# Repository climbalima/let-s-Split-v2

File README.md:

[Easier to use dimensions document](https://cad.onshape.com/documents/c6e5ae250d1e24fe46c9ef6c/w/d69f7049c0921df3d2b241f9/e/8fe93acf5ce0a952a4563ee0) 

Just click on any two lines/points, and read the dimensions bottom left. Space to unselect everything.

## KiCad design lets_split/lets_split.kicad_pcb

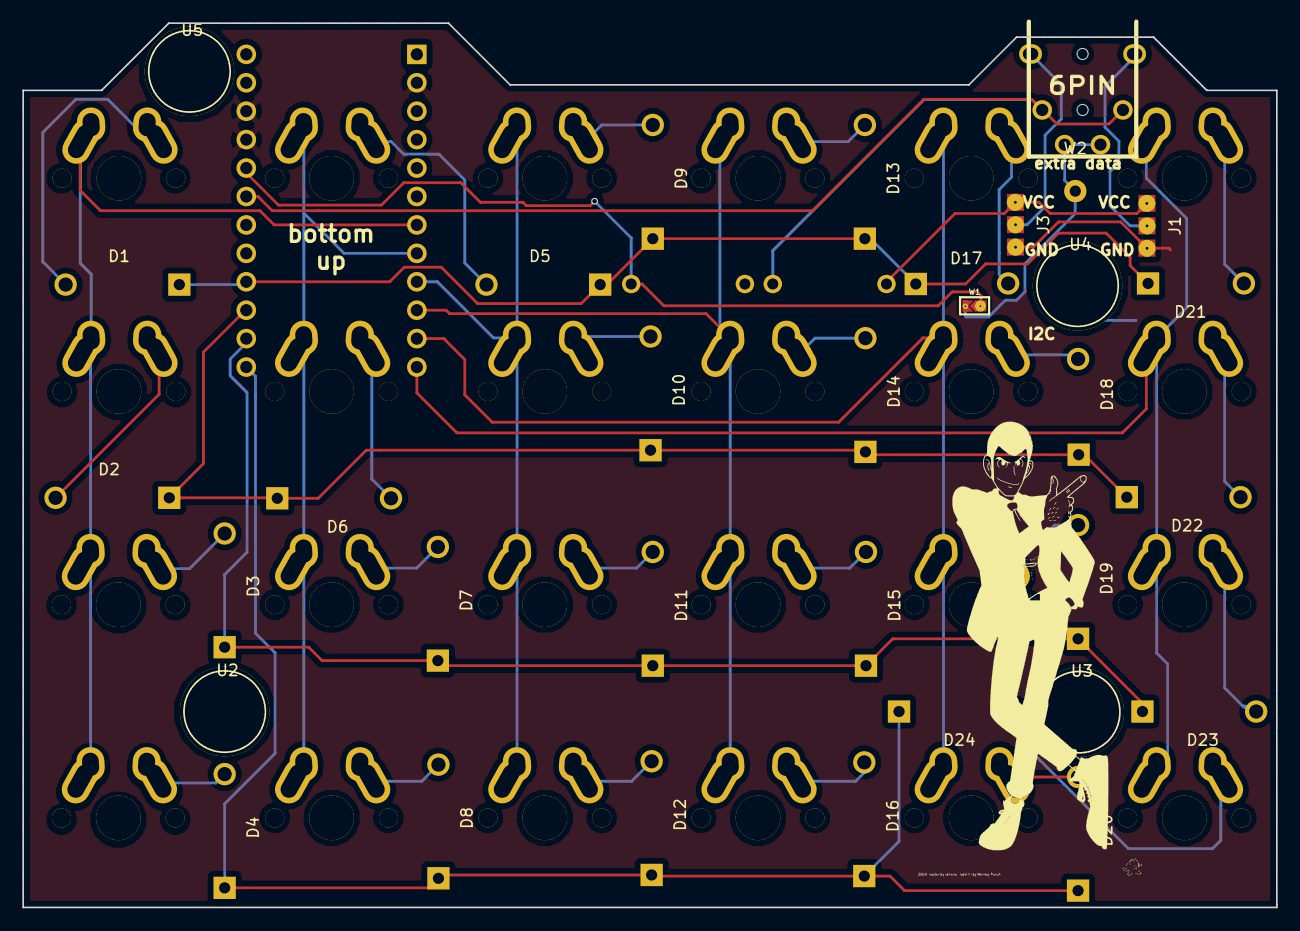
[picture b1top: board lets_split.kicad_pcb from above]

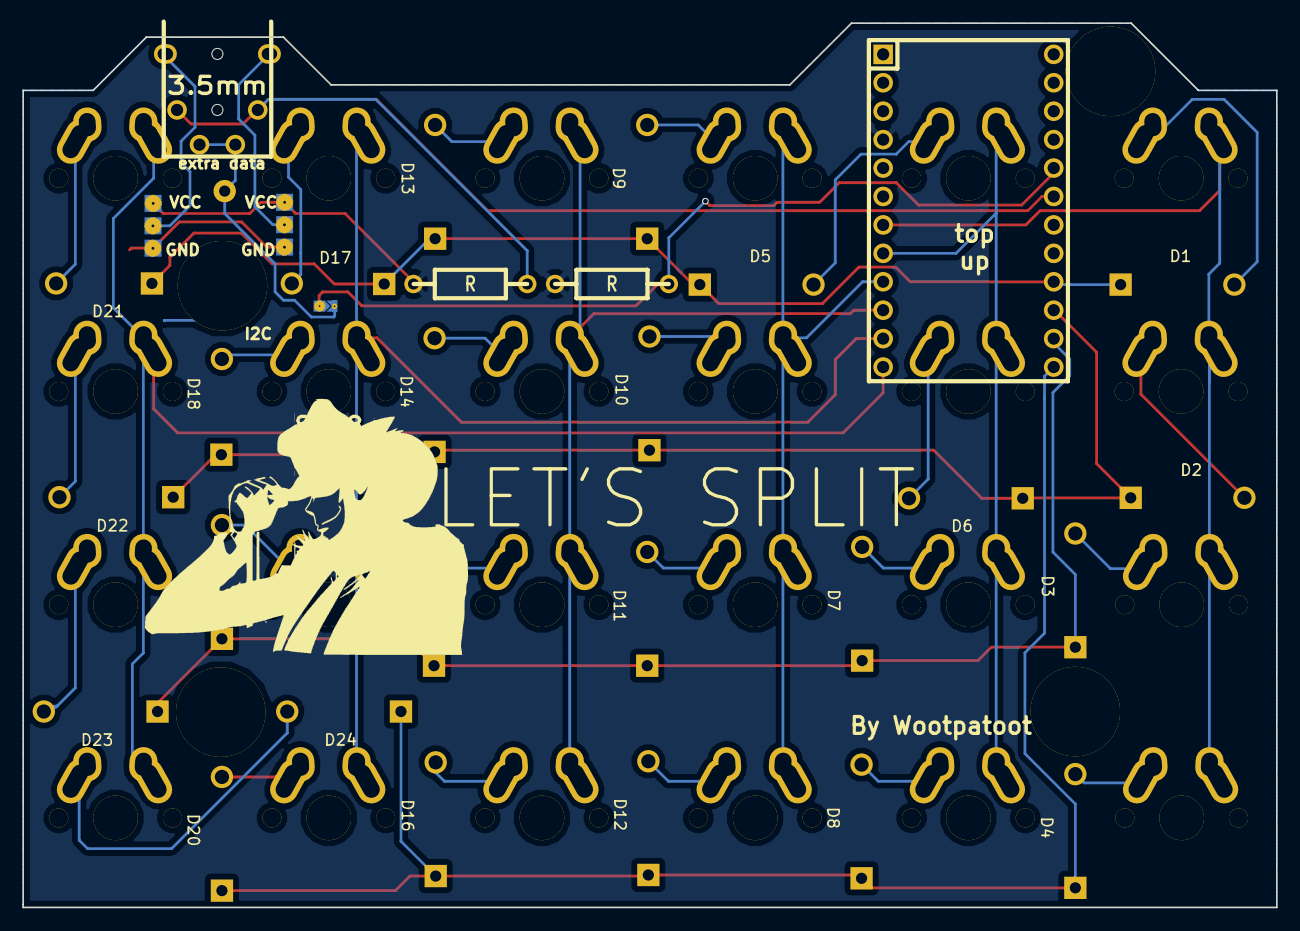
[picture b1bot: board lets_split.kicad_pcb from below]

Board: 2 copper layers, 112.0 x 79.0 mm, 58 parts (3 on the bottom side), 39 nets.

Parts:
D1, D2, D3, D4, D5, D6, D7, D8, D9, D10, D11, D12, D13, D14, D15, D16, D17, D18, D19, D20, D21, D22, D23, D24: D; Diode_DO-41_SOD81_Horizontal_RM10
J1, J3: 3PIN; jumper
J2: 6PIN; 4pin35mmAudio
R1, R2: R; RESISTOR
SW1, SW2, SW3, SW4, SW5, SW6, SW7, SW8, SW9, SW10, SW11, SW12, SW13, SW14, SW15, SW16, SW17, SW18, SW19, SW21, SW22, SW23: SW_PUSH; MXALPS_FLIP
U1: TEENSY_2.0
U2, U3, U4, U5: HOLE
W1: TEST; JUMPER_SMD_2DUB
W2: TEST_1P; SolderWirePad_single_2mmDrill

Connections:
GND: J1.1, J3.1, U1.2, U1.26, U1.27
unnamed: D1.2, SW1.2
unnamed: D2.2, SW2.2
unnamed: D3.2, SW3.2
unnamed: D4.2, SW4.2
unnamed: D5.2, SW5.2
unnamed: D6.2, SW6.2
unnamed: D7.2, SW7.2
unnamed: D8.2, SW8.2
unnamed: D9.2, SW9.2
unnamed: D10.2, SW10.2
unnamed: D11.2, SW11.2
unnamed: D12.2, SW12.2
unnamed: D13.2, SW13.2
unnamed: D14.2, SW14.2
unnamed: D15.2, SW15.2
unnamed: D16.2, SW16.2
unnamed: D17.2, SW17.2
unnamed: D18.2, SW18.2
unnamed: D19.2, SW19.2
unnamed: D21.2, SW21.2
unnamed: D22.2, SW22.2
unnamed: D23.2, SW23.2
unnamed: J1.2, J2.1
unnamed: J2.4, J3.2
unnamed: R1.2, U1.25, W1.2
VCC: J1.3, J3.3, R1.1, R2.2, U1.4
col0: SW1.1, SW2.1, SW3.1, SW4.1, U1.7
col1: SW5.1, SW6.1, SW7.1, SW8.1, U1.8
col2: SW9.1, SW10.1, SW11.1, SW12.1, U1.9
col3: SW13.1, SW14.1, SW15.1, SW16.1, U1.10
col4: SW17.1, SW18.1, SW19.1, U1.11
col5: SW21.1, SW22.1, SW23.1, U1.12
data: J2.2, J2.6, R2.1, U1.24
row0: D1.1, D5.1, D9.1, D13.1, D17.1, D21.1, U1.21
row1: D2.1, D6.1, D10.1, D14.1, D18.1, D22.1, U1.20
row2: D3.1, D7.1, D11.1, D15.1, D19.1, D23.1, U1.19
row3: D4.1, D8.1, D12.1, D16.1, D20.1, D24.1, U1.18
xtradata: J2.3, J2.5, W1.1, W2.1

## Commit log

2017-04-17 added files
2017-04-17 Create Liscence
2017-04-19 Spelling in `License` filename
2017-10-08 Added dimension SVG
2017-10-08 Added dimention image to readme
2017-10-08 Added CAD doc to readme
2017-10-08 Honey I shrunk the svg
2018-04-03 Fix column 1 spacing
2019-10-31 Fix alignments at left column
